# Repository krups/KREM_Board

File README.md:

# KREM_Board
Eagle files for the main KREM electronics board

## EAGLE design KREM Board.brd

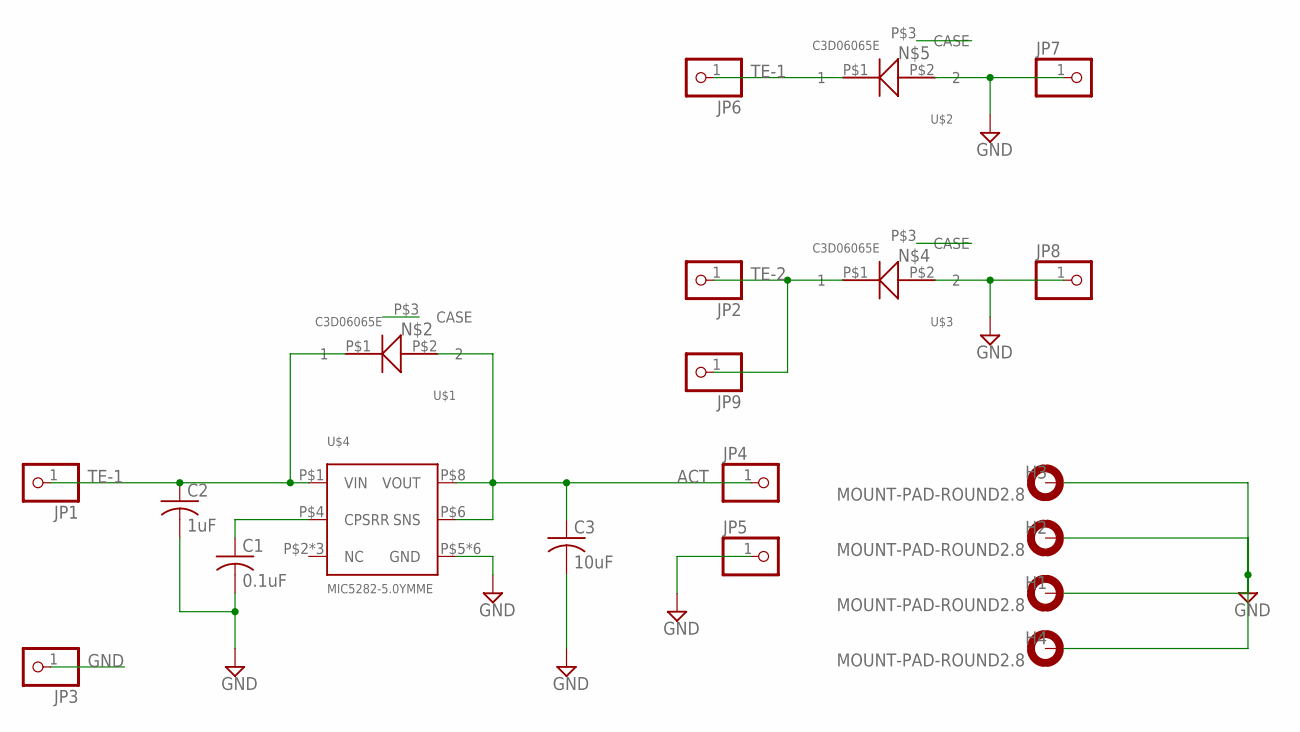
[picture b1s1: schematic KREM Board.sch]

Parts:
C1: 0.1uF; C2220K
C2: 1uF; C2220K
C3: 10uF; C2220K
H1, H2, H3, H4: MOUNT-PAD-ROUND2.8; 2,8-PAD
JP1, JP2, JP3, JP4, JP5, JP6, JP7, JP8, JP9: PINHD-1X1; 1X01
U$1, U$2, U$3: C3D06065E; TO-252
U$4: MIC5282-5.0YMME; MSOP8-EPAD

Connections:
ACT: C3.1, JP4.1, U$1.P$2 (2), U$4.P$6 (SNS), U$4.P$8 (VOUT)
GND: C1.2, C2.2, C3.2, H1.B2,8, H2.B2,8, H3.B2,8, H4.B2,8, JP3.1, JP5.1, JP7.1, JP8.1, U$2.P$2 (2), U$3.P$2 (2), U$4.P$5 (GND), U$4.P$9 (GND), U$4.P$10 (GND), U$4.P$11 (GND), U$4.P$12 (GND), U$4.P$13 (GND)
unnamed: C1.1, U$4.P$4 (CPSRR)
TE-1: C2.1, JP1.1, JP6.1, U$1.P$1 (1), U$2.P$1 (1), U$4.P$1 (VIN)
TE-2: JP2.1, JP9.1, U$3.P$1 (1)

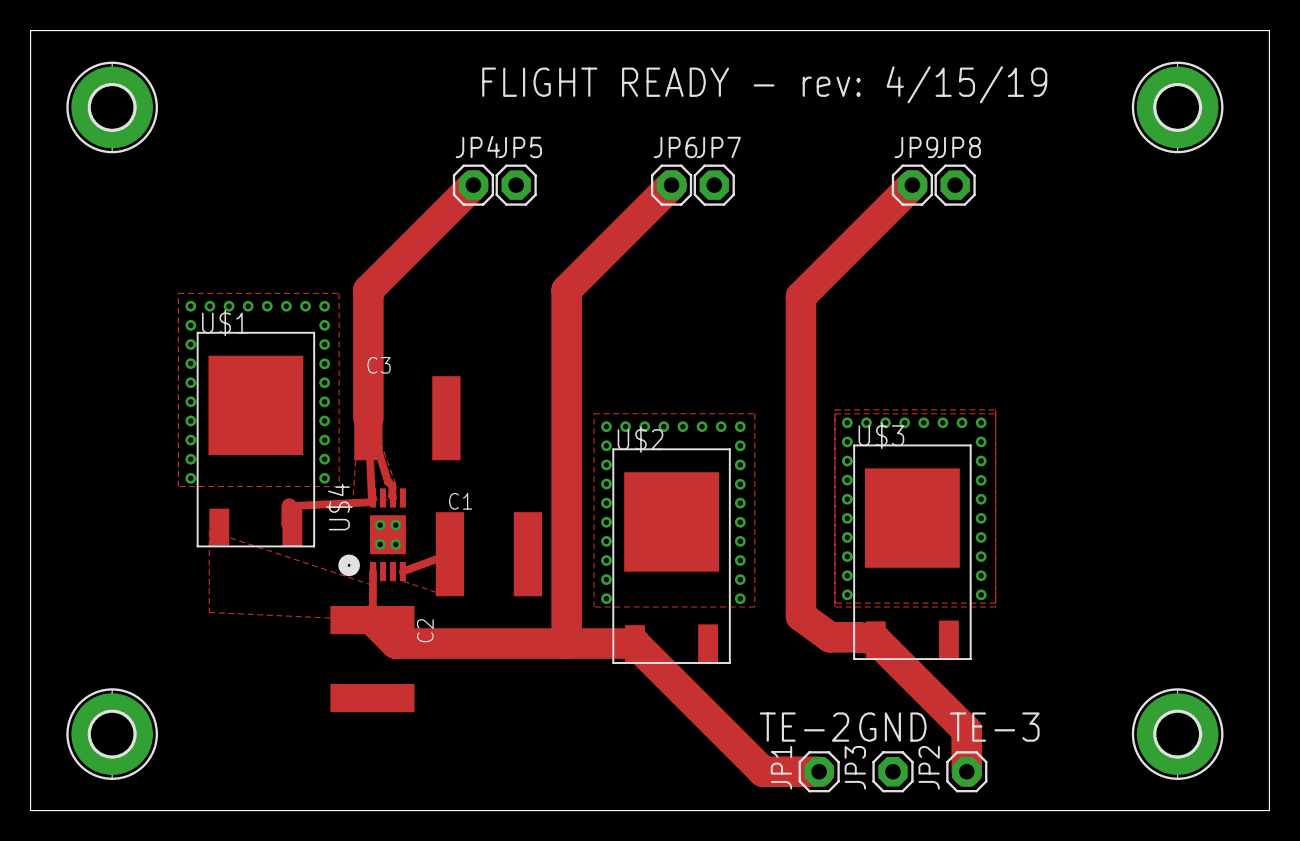
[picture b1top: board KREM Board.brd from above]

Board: 2 copper layers, 81.0 x 51.0 mm, 20 parts (0 on the bottom side), 5 nets.

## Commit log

2019-05-16 Removed resistor on TE-2, added mouting holes, moved input pins, updated revision date
2019-05-16 Raised isolation to .4064 on ground plane

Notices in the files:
parts and their libraries:
SparkFun-Aesthetics: Licensing: Creative Commons ShareAlike 4.0 International - https://creativecommons.org/licenses/by-sa/4.0
